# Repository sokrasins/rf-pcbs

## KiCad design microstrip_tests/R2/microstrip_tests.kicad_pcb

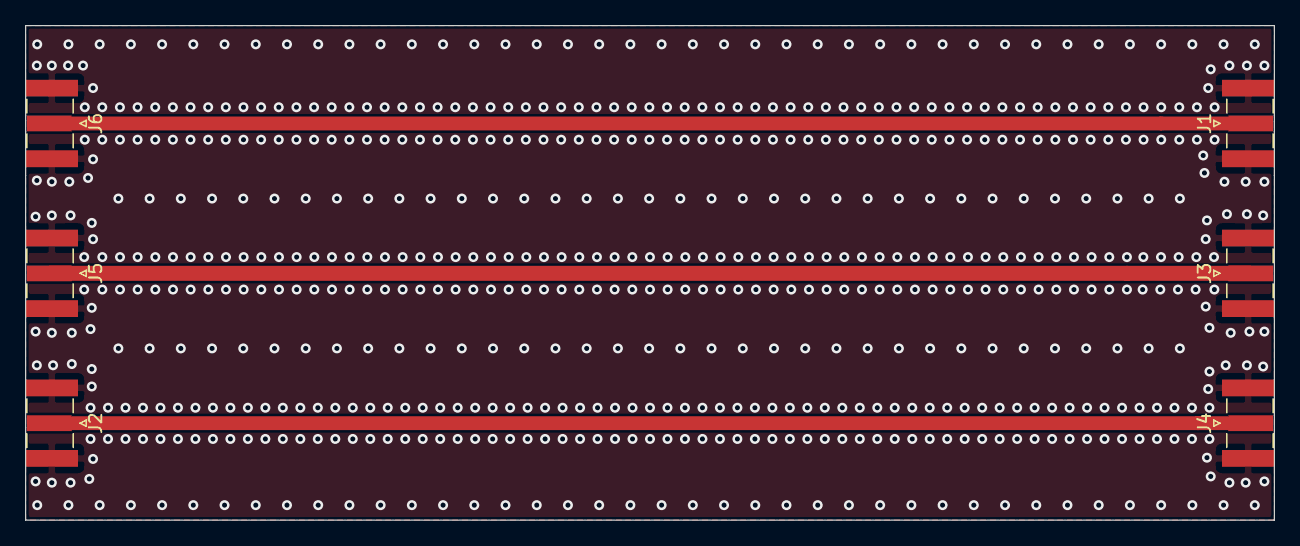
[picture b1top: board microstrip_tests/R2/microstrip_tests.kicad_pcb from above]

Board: 2 copper layers, 100.0 x 39.6 mm, 6 parts (0 on the bottom side), 4 nets.

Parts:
J1, J2, J3, J4, J5, J6: Conn_Coaxial; SMA_Samtec_SMA-J-P-X-ST-EM1_EdgeMount

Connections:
GND: J1.2, J2.2, J3.2, J4.2, J5.2, J6.2
unnamed: J1.1, J6.1
unnamed: J2.1, J4.1
unnamed: J3.1, J5.1

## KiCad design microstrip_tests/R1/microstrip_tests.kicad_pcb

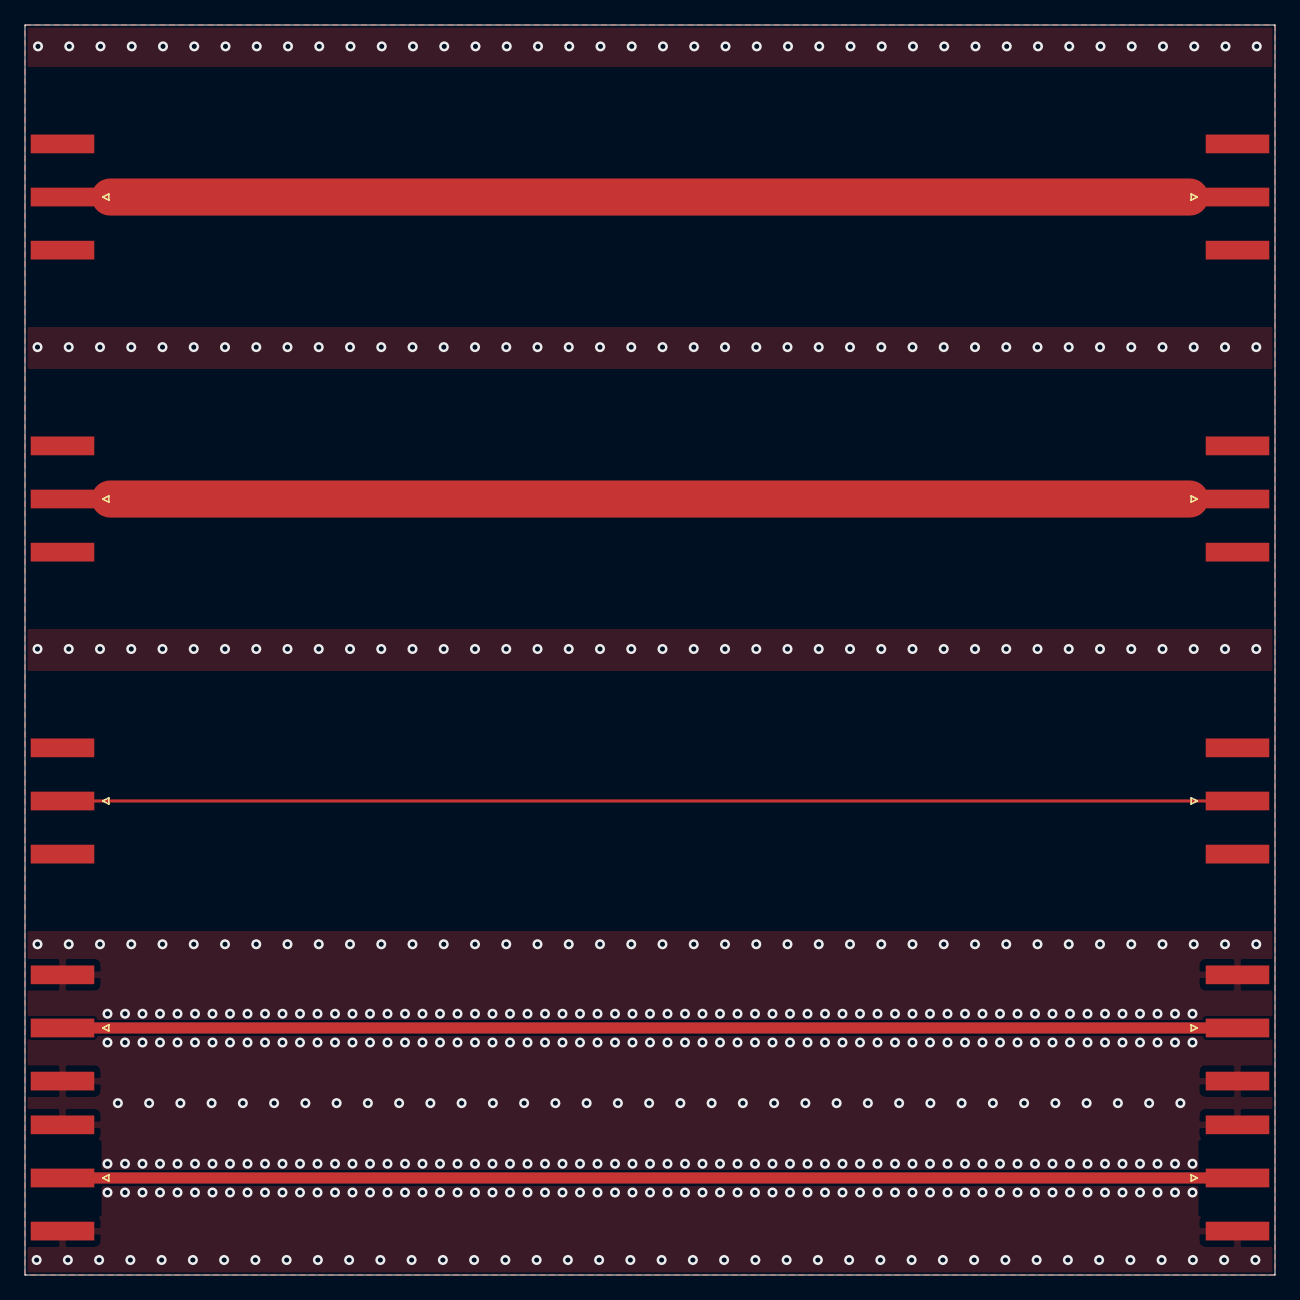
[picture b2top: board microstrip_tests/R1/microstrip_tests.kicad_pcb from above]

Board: 2 copper layers, 100.0 x 100.0 mm, 10 parts (0 on the bottom side), 6 nets.

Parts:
J1, J2, J3, J4, J5, J6, J7, J8, J9, J10: Conn_Coaxial; SMA_Amphenol_132289_EdgeMount

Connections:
GND: J1.2, J2.2, J3.2, J4.2, J5.2, J6.2, J7.2, J8.2, J9.2, J10.2
unnamed: J1.1, J2.1
unnamed: J3.1, J6.1
unnamed: J4.1, J7.1
unnamed: J5.1, J8.1
unnamed: J9.1, J10.1

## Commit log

2020-07-11 push rf pcb examples
2020-07-12 Add rf detector dev board docs
2020-07-16 Add new dircoup datasheet
